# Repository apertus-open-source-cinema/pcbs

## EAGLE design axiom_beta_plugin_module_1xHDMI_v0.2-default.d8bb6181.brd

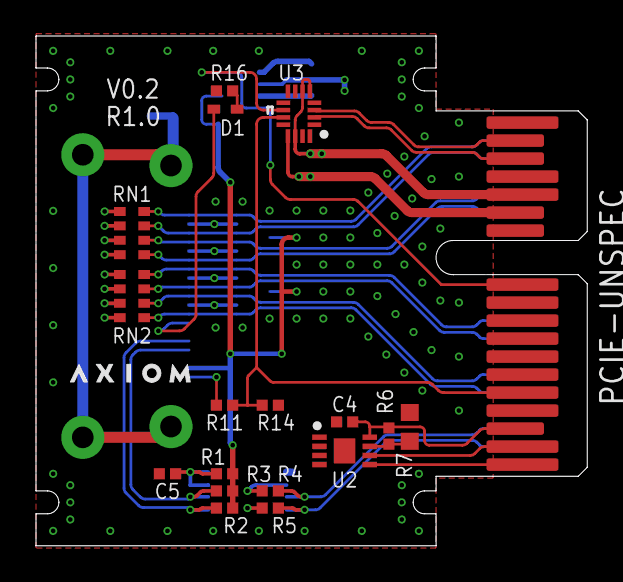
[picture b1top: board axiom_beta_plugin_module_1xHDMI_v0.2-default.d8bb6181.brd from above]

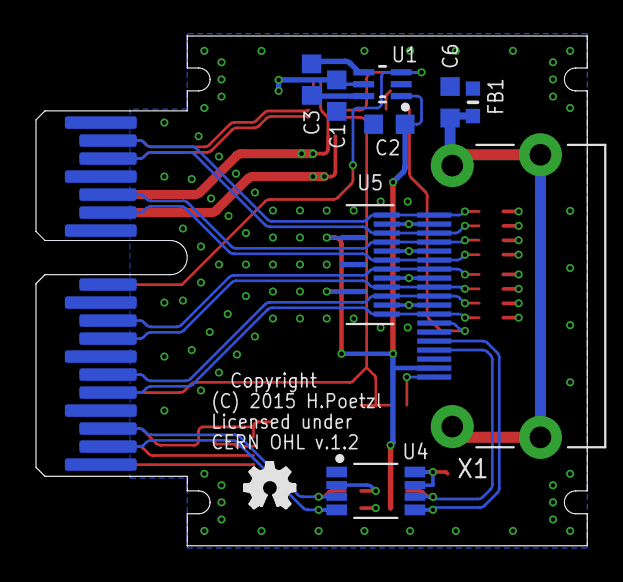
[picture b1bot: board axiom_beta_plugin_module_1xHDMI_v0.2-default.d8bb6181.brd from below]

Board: 4 copper layers, 30.6 x 28.3 mm, 29 parts (10 on the bottom side), 31 nets.

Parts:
C1, C2, C3, C6: C0603K
C4, C5: 0402-B
D1: SOD523
FB1: _0603MP
LOGO2: OSHW_LOGO_FILLX0100-NT; OSHW_FILLX100_NOTEXT
PCIE-UNSPEC: PCIE-36-AXIOM
R1, R2, R3, R4, R5, R6, R11, R14, R16: 0402-B
R7: 0603-B
RN1, RN2: 49R9; CAY16
U1: REG710P6X; SOT65P210X110-6N
U2: BR24G04NUX; DFN200X300X100-9N
U3: SN74AVC4T774RSV; QFN40P185X265X55-16N
U4: GTL2002DP; TSSOP-8
U5: TPD8S009; R-PDSO-N15
U$1: AXIOM_LOGO262X40; AXIOM_LOGO_262X40
X1: HDMI-10029449; 10029449-X01XLF

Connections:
+5V: C2.1, R1.2, R2.2, R3.2, U1.1, U5.13, U5.15, X1.18
A_3_N: PCIE-UNSPEC.A16, RN1.3, U5.10, X1.3
A_3_P: PCIE-UNSPEC.A17, RN1.4, U5.12, X1.1
A_5_N: PCIE-UNSPEC.A8, RN2.3, U5.4, X1.9
A_5_P: PCIE-UNSPEC.A9, RN2.4, U5.6, X1.7
A_7_N: PCIE-UNSPEC.A13, RN1.1, U5.7, X1.6
A_7_P: PCIE-UNSPEC.A14, RN1.2, U5.9, X1.4
A_9_N: PCIE-UNSPEC.A5, RN2.1, U5.1, X1.12
A_9_P: PCIE-UNSPEC.A6, RN2.2, U5.3, X1.10
B_2_N: PCIE-UNSPEC.A2, R5.2, U4.4
B_2_P: PCIE-UNSPEC.A3, R4.2, U4.3
EN: PCIE-UNSPEC.B11, U1.3, U3.10
GND: C1.2, C2.2, C4.2, C5.1, C6.2, FB1.2, PCIE-UNSPEC.A1, PCIE-UNSPEC.A4, PCIE-UNSPEC.A7, PCIE-UNSPEC.A10, PCIE-UNSPEC.A12, PCIE-UNSPEC.A15, PCIE-UNSPEC.A18, PCIE-UNSPEC.B15, PCIE-UNSPEC.B18, R7.2, R14.2, U1.2, U2.1, U2.2, U2.3, U2.4, U2.EP, U3.7, U3.8, U3.15, U3.16, U4.1, U5.2, U5.5, U5.8, U5.11, X1.2, X1.5, X1.8, X1.11, X1.17
HDMI_CEC: D1.C, X1.13
HDMI_HP: R11.1, X1.19
HDMI_SCL: R2.1, U4.5, X1.15
HDMI_SDA: R3.1, U4.6, X1.16
HP: PCIE-UNSPEC.B5, R11.2, R14.1, U3.11
I2C_V: C4.1, PCIE-UNSPEC.B3, R6.1, U2.8
JX2_18_N: PCIE-UNSPEC.B17, U3.3
JX2_18_P: PCIE-UNSPEC.B16, U3.2
unnamed: C3.1, U1.6
unnamed: C3.2, U1.4
unnamed: R6.2, R7.1, U2.7
unnamed: C6.1, FB1.1, X1.Z1, X1.Z2, X1.Z3, X1.Z4
unnamed: D1.A, R16.2
unnamed: C5.2, R1.1, U4.7, U4.8
PCIE_VCC: C1.1, PCIE-UNSPEC.B13, U1.5, U3.13
PCIE_VCCIO: PCIE-UNSPEC.B14, R4.1, R5.1, RN1.5, RN1.6, RN1.7, RN1.8, RN2.5, RN2.6, RN2.7, RN2.8, U3.5, U3.6, U3.14, U4.2
SCL: PCIE-UNSPEC.B2, U2.6
SDA: PCIE-UNSPEC.B1, U2.5

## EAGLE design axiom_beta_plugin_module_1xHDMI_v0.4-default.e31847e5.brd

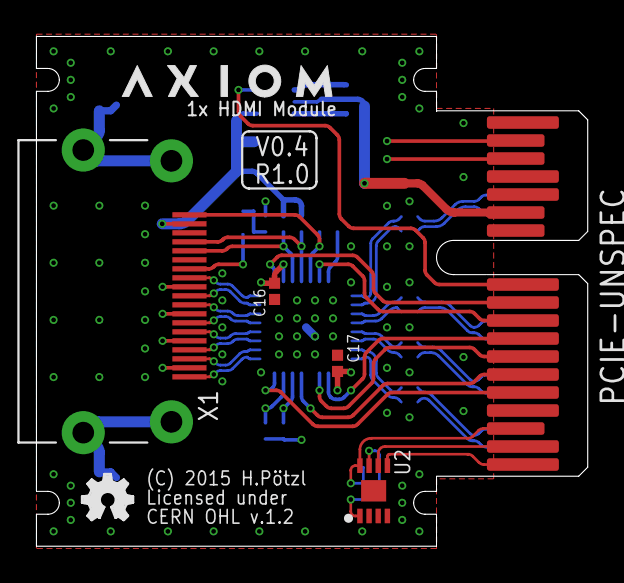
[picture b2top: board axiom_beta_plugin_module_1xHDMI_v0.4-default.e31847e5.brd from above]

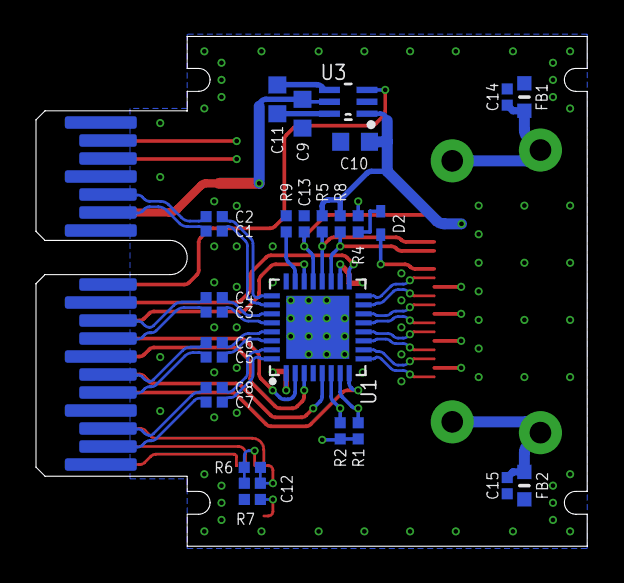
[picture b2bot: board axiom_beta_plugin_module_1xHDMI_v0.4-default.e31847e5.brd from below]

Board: 4 copper layers, 30.6 x 28.3 mm, 35 parts (28 on the bottom side), 51 nets.

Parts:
C1, C2, C3, C4, C5, C6, C7, C8, C12, C13, C14, C15, C16, C17: 0402-B
C9, C10, C11: 0603-B
D2: SOD523
FB1, FB2: _0603MP
LOGO2: OSHW_LOGO_FILLX0100-NT; OSHW_FILLX100_NOTEXT
PCIE-UNSPEC: PCIE-36-AXIOM
R1, R2, R4, R5, R6, R7, R8, R9: 0402-B
U1: PTN3363; HVQFN32
U2: BR24G04NUX; DFN200X300X100-9N
U3: REG710P6X; SOT65P210X110-6N
U$1: AXIOM_LOGO459X70; AXIOM_LOGO_459X70
X1: HDMI-10029449; 10029449-X01XLF

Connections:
3V3: C16.1, C17.1, R1.1, R2.1, R4.1, U1.1, U1.18
5V0: C10.1, R5.1, R8.1, U3.1, X1.18
!OE!: PCIE-UNSPEC.B10, U1.17
CLOCK_N: U1.16, X1.12
CLOCK_P: U1.15, X1.10
DATA0_N: U1.14, X1.9
DATA0_P: U1.13, X1.7
DATA1_N: U1.12, X1.6
DATA1_P: U1.11, X1.4
DATA2_N: U1.10, X1.3
DATA2_P: U1.9, X1.1
DDC_EN: PCIE-UNSPEC.B9, U1.22
DDET: PCIE-UNSPEC.B7, U1.3
EN: PCIE-UNSPEC.B11, U3.3
EQ0: PCIE-UNSPEC.B5, U1.8
EQ1: PCIE-UNSPEC.B8, U1.2
GND: C9.2, C10.2, C12.2, C13.2, C14.2, C15.2, C16.2, C17.2, FB1.2, FB2.2, PCIE-UNSPEC.A1, PCIE-UNSPEC.A4, PCIE-UNSPEC.A7, PCIE-UNSPEC.A10, PCIE-UNSPEC.A12, PCIE-UNSPEC.A15, PCIE-UNSPEC.A18, PCIE-UNSPEC.B15, PCIE-UNSPEC.B18, R7.2, R9.2, U1.24, U1.33, U2.1, U2.2, U2.3, U2.4, U2.EP, U3.2, X1.2, X1.5, X1.8, X1.11, X1.17
HDMI_CEC: D2.C, X1.13
HDMI_HP: C13.1, U1.21, X1.19
HDMI_SCL: R8.2, U1.19, X1.15
HDMI_SDA: R5.2, U1.20, X1.16
I2C_V: C12.1, PCIE-UNSPEC.B3, R6.1, U2.8
IHP: PCIE-UNSPEC.B6, U1.5
IN_D1_N: C2.1, U1.25
IN_D1_P: C1.1, U1.26
IN_D2_N: C4.1, U1.27
IN_D2_P: C3.1, U1.28
IN_D3_N: C6.1, U1.29
IN_D3_P: C5.1, U1.30
IN_D4_N: C8.1, U1.31
IN_D4_P: C7.1, U1.32
ISCL: R1.2, U1.7
ISDA: R2.2, U1.6
LVDS_0_N: C8.2, PCIE-UNSPEC.A3
LVDS_0_P: C7.2, PCIE-UNSPEC.A2
LVDS_1_N: C6.2, PCIE-UNSPEC.A6
LVDS_1_P: C5.2, PCIE-UNSPEC.A5
LVDS_2_N: C4.2, PCIE-UNSPEC.A9
LVDS_2_P: C3.2, PCIE-UNSPEC.A8
LVDS_3_N: C2.2, PCIE-UNSPEC.A14
LVDS_3_P: C1.2, PCIE-UNSPEC.A13
unnamed: C11.1, U3.6
unnamed: C11.2, U3.4
unnamed: C14.1, FB1.1, X1.Z1, X1.Z2
unnamed: R6.2, R7.1, U2.7
unnamed: C15.1, FB2.1, X1.Z3, X1.Z4
unnamed: R9.1, U1.23
unnamed: D2.A, R4.2
PCIE_VCC: C9.1, PCIE-UNSPEC.B13, U3.5
SCL: PCIE-UNSPEC.B2, U2.6
SDA: PCIE-UNSPEC.B1, U2.5

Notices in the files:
axiom_beta_plugin_module_1xHDMI_v0.2-default.d8bb6181.brd:
(C) 2015 H.Poetzl
Licensed under
CERN OHL v.1.2
axiom_beta_plugin_module_1xHDMI_v0.4-default.e31847e5.brd:
(C) 2015 H.Pötzl
parts and their libraries:
microbuilder: This work is placed in the public domain, and may be freely used for commercial and non-commercial work with the following conditions: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
